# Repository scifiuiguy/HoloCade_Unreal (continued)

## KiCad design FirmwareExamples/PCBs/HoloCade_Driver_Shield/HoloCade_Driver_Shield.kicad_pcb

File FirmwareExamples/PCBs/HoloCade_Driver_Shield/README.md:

# HoloCade Driver Shield

**Also known as:** LBDS, Driver Shield

## Overview

**Motor Control ECU for High-Current Actuator Applications:**

The HoloCade Driver Shield ("LBDS" or "Driver Shield") is a specialized ECU derived from the Universal Shield, designed for high-current motor control applications. It integrates a BTS7960 H-bridge motor driver with hall sensor feedback support, while maintaining the core connectivity features of the Universal Shield (Ethernet, CAN-FD, and aux ports).

<details>
<summary><strong>Driver Shield is a Motor Control ECU</strong></summary>

<div style="margin-left: 20px;">

The Driver Shield is based on the Universal Shield architecture but replaces 4 of the 8 aux ports with an integrated BTS7960 H-bridge motor driver. This enables direct control of high-current linear actuators (such as the PA-HD1-HALL) with integrated hall sensor feedback for position sensing. The shield maintains full compatibility with the Universal Shield's networking and communication features (Ethernet, CAN-FD) while adding dedicated motor control capabilities.

</div>

</details>

<details>
<summary><strong>Key Features</strong></summary>

<div style="margin-left: 20px;">

- Multi-platform support: ESP32-S3 (native) & STM32/Arduino (via personality adapters)
- 4× CAT5 aux ports for child ECUs (Raspberry Pi, Jetson, ESP32, STM32, Arduino)
- Integrated BTS7960 H-bridge motor driver (30A per half-bridge, 60A total)
- Hall sensor feedback support (2× ADC channels for position sensing)
- Isolated CAN-FD transceiver for high-current device control
- 100 Mbps Ethernet connectivity
- 12V/24V input with 5V power distribution (≥5A total capacity)
- 24V motor power rail (direct from input, bypasses buck converter)
- Designed for potting and long-term installations

</div>

</details>

<details>
<summary><strong>High-Level Component Diagram</strong></summary>

<div style="margin-left: 20px;">

```
          ┌────────────────────────────────────────┐
          |                                        │
    ┌─────▲───────┐    ┌───────┐ +5V               │
    │ Barrel Jack │───→│LM2576 │────┐       ┌──────▼───────┐
    │  12V/24V    │    │ Buck  │    │       │ 12/24V Fan   │
    └─────────────┘    └───────┘    │       └───────┬──────┘
         │                │+5V     │               ▼
         │                │        │  ┌────────────────────────┐
         │                │        └─→│         ESP32-S3       │
         │                │           │      (Motherboard)     │
         │                │           └──▲──────────────▲──────┘
         │                │              │              │
         │                │         ┌────▼────┐    ┌────▼────┐
         │                │         │LAN8720A │    │ADM3057E │
         │                │         │Ethernet │    │ CAN-FD  │
         │                │         └────▲────┘    └────▲────┘
         │                │              │              │
         │                │              │         ┌────▼─────┐
         │                │              │         │CAN 3-pin │
         │                │              │         └──────────┘         
         │                │              │
         │                │    ┌─────────▼───────────────┐   
         │                │    │  Aux Ports: J5 J6 J7 J8 │   
         │                │    │  (4× RJ45: Ethernet)    │   
         │                │    └─────────────────────────┘   
         │                │
         │                └──→ 5V to MCU VIN
         │
         └──→ 24V Motor Power Rail
                │
                └──→ Motor Driver Sheet
                      ├─→ BTS7960 H-Bridge (×2)
                      ├─→ 74HC244 Buffer IC
                      ├─→ MBR3045PT Dual-Channel Schottky Diode
                      └─→ Molex 6-pin Actuator Connector (PA-HD1-HALL)
                                              
```

</div>

</details>

<details>
<summary><strong>Project Files</strong></summary>

<div style="margin-left: 20px;">

- **HoloCade_Driver_Shield.kicad_pro** - KiCAD project file
- **HoloCade_Driver_Shield.kicad_sch** - Main schematic file (Sheet 1)
- **motor-driver.kicad_sch** - Motor driver hierarchical sheet (Sheet 2)
- **HoloCade_Driver_Shield.kicad_pcb** - PCB layout file

**Note:** The Driver Shield uses a hierarchical schematic design with the motor driver components on a separate sheet for better organization.

</div>

</details>

<details>
<summary><strong>Power Architecture</strong></summary>

<div style="margin-left: 20px;">

**Hybrid Approach:**
```
12V/24V Input (Barrel Jack)
    ↓
    ├─→ Buck Converter (LM2576: 12V/24V → 5V, 60V max input)
    │       ↓
    │       ├─→ 5V to MCU VIN (via adapter)
    │       │       ↓
    │       │   MCU Onboard Regulator (5V → 3.3V)
    │       │       ↓
    │       │   MCU 3.3V Output (via adapter)
    │       │       └─→ Shield Logic Components (LAN8720A, LEDs)
    │       │
    │       └─→ 5V directly to Aux Port Pins 4 (≥5.0A total across 4 ports)
    │
    └─→ 24V Motor Power Rail (direct passthrough, bypasses buck converter)
            ↓
        Motor Driver Sheet
            ├─→ BTS7960 H-Bridge (×2) - VS pins
            └─→ Actuator Power (MOTOR_A_OUT, MOTOR_B_OUT)
```

**Key Points:**
- Buck converter (LM2576HVS-5) handles 12V/24V input (up to 29.2V for fully charged 24V LiFePO4)
- Aux port power: 5V directly from buck converter (≥5.0A total capacity across 4 ports)
- Motor power: 24V direct passthrough from barrel jack (bypasses buck converter)
- Shield logic: 3.3V from ESP32-S3 pins 1-2 (3.3V_OUT)
- High-current MCUs (ESP32-S3, STM32F407): Adapter routes MCU 3.3V directly
- Low-current MCUs (Arduino): Adapter includes 3.3V regulator (AMS1117-3.3)

</div>

</details>

<details>
<summary><strong>Components</strong></summary>

<div style="margin-left: 20px;">

### Primary Components (Sheet 1 - Shared with Universal Shield)

**Primary ICs (Sheet 1):**
- **U1** - LM2576HVS-5 (TO-220/TO-263) - Buck converter (12V/24V → 5V, ≥5A, 60V max input)
- **U2-U5** - MTJ-883X1 (RJ45 aux ports J5-J8, references U2, U3, U4, U5 in schematic)
- **U6** - ESP32-S3-2x22 (MCU interface, 44-pin header)
- **U7** - ADM3057ExRW - Isolated CAN-FD transceiver (3kV isolation)
- **U8** - LAN8720A (QFN-32) - 100 Mbps Ethernet PHY
  - Management: MDC/MDIO to MCU via adapter
  - Clock: External 25MHz crystal (3225 SMD recommended, Y1)
  - Reset: ESP32-S3 EN pin (GPIO3) or separate GPIO

**3.3V Power:** ESP32-S3 pins 1-2 (3.3V_OUT) provide 3.3V for shield logic components. No separate 3.3V LDO required for ESP32-S3.
- VIO: +3.3V (logic supply) - decoupled with C14 (100nF)
- VCC: +5V (isoPower supply) - decoupled with C15 (100nF) and C16 (4.7µF tantalum)
- VISOOUT → VISOIN (Kelvin jumper required on PCB layout)
- VISOIN/VISOOUT: Isolated supply - decoupled with C17 (100nF) and C18 (4.7µF tantalum)
- CAN termination: 120Ω resistor (R12) switchable via SW1 (DIP switch) across CANH/CANL

**LEDs (3 total):**
- Power LED (Red): +3.3V → R4 (270Ω) → D1 → GND
- Ethernet Link LED (Green): LAN8720A LED1 → R5 (270Ω) → D2 → GND
- Ethernet Speed LED (Green): LAN8720A LED2 → R6 (270Ω) → D3 → GND

**Resistors (Sheet 1 - standard components):**

| Reference | Value | Purpose | Notes |
|-----------|-------|---------|-------|
| R1 | 10 kΩ | Polarity protection MOSFET gate pull-down | Pulls gate of IRF9540N P-channel MOSFET to GND for reverse polarity protection |
| R2 | 1 kΩ | Buck converter voltage divider (upper) | Forms feedback divider with R3 for LM2576 output regulation |
| R3 | 326Ω | Buck converter voltage divider (lower) | Forms feedback divider with R2 for LM2576 5V output regulation |
| R4 | 270Ω | Power LED current limiting | Limits current through red power indicator LED (D1) |
| R5 | 270Ω | Ethernet Link LED current limiting | Limits current through green LAN LED1 (D2, link status) |
| R6 | 270Ω | Ethernet Speed LED current limiting | Limits current through green LAN LED2 (D3, speed indicator) |
| R7 | 49.9Ω (49R9) | LAN8720A RBIAS pull-down | Sets bias current for LAN8720A internal reference |
| R8 | 10 kΩ | ESP32-S3 RESET_N pull-up | Pull-up resistor for LAN8720A RESET_N pin (active LOW) |
| R9 | 4.7 kΩ | LAN8720A MDIO pull-up | Pull-up resistor for ESP32-S3 GPIO18 (MDIO) management interface |
| R10 | 100Ω | Fan FET gate resistor | Current limiting resistor for IRLZ44N MOSFET gate drive (GPIO42) |
| R11 | 10 kΩ | Fan FET gate pull-down | Pull-down resistor for fan MOSFET gate (prevents floating when GPIO42 is high-Z) |
| R12 | 120Ω | CAN bus termination resistor | Switchable termination resistor across CANH/CANL (via SW1) |

**Capacitors (Sheet 1 - standard components):**

| Reference | Value | Type | Purpose | Notes |
|-----------|-------|------|---------|-------|
| C1 | 100nF | Non-polarized | Barrel jack output decoupling | High-frequency noise filtering on power input |
| C2 | 10µF | Polarized | Barrel jack output decoupling | Bulk capacitance for power input smoothing |
| C3 | 100nF | Non-polarized | Buck converter input decoupling | High-frequency noise filtering on LM2576 input |
| C4 | 100nF | Non-polarized | Buck converter output decoupling | High-frequency noise filtering on 5V output |
| C5 | 10µF | Polarized | Buck converter output decoupling | Bulk capacitance for 5V output smoothing |
| C6 | 10µF | Polarized | ESP32-S3 3.3V output decoupling | Bulk capacitance for ESP32 3.3V_OUT smoothing |
| C7 | 100nF | Non-polarized | ESP32-S3 3.3V output decoupling | High-frequency noise filtering on ESP32 3.3V_OUT |
| C8 | 100nF | Non-polarized | LAN8720A VDD2 decoupling | Power supply decoupling for LAN8720A VDD2 pin |
| C9 | 100nF | Non-polarized | LAN8720A VDDCR decoupling | Power supply decoupling for LAN8720A VDDCR pin |
| C10 | 100nF | Non-polarized | LAN8720A VDD1A decoupling | Power supply decoupling for LAN8720A VDD1A pin |
| C11 | 100nF | Non-polarized | LAN8720A VDDIO decoupling | Power supply decoupling for LAN8720A VDDIO pin |
| C12 | 10pF | Non-polarized | 25MHz crystal load capacitor (XTAL1) | Crystal oscillator load capacitor for XTAL1 |
| C13 | 10pF | Non-polarized | 25MHz crystal load capacitor (XTAL2) | Crystal oscillator load capacitor for XTAL2 |
| C14 | 100nF | Non-polarized | ADM3057E VIO decoupling | High-frequency noise filtering on CAN transceiver logic supply |
| C15 | 100nF | Non-polarized | ADM3057E VCC decoupling | High-frequency noise filtering on CAN transceiver isoPower supply |
| C16 | 4.7µF | Polarized (Tantalum) | ADM3057E VCC bulk decoupling | Bulk capacitance for CAN transceiver isoPower supply smoothing |
| C17 | 100nF | Non-polarized | ADM3057E VISO decoupling | High-frequency noise filtering on CAN transceiver isolated supply (VISOIN/VISOOUT) |
| C18 | 4.7µF | Polarized (Tantalum) | ADM3057E VISO bulk decoupling | Bulk capacitance for CAN transceiver isolated supply smoothing |

**Diodes (Sheet 1 - standard components):**

| Reference | Type | Value | Purpose | Notes |
|-----------|------|-------|---------|-------|
| D1 | LED | LED | Red status LED for 3V power | Power indicator LED, current limited by R4 (270Ω) |
| D2 | LED | LED | Green status LED for LAN LED1 pin | Ethernet link status indicator, driven by LAN8720A LED1, current limited by R5 (270Ω) |
| D3 | LED | LED | Green status LED for LAN LED2 pin | Ethernet speed indicator, driven by LAN8720A LED2, current limited by R6 (270Ω) |
| D4 | Schottky Diode | SS14 | Flyback diode for MCU fan protection | Protects MCU from inductive kickback when fan MOSFET switches off (cathode on +VIN, anode on FAN_SW) |
| D5 | Zener Diode | BZX84C12 | Polarity protection MOSFET gate protection | 12V zener diode protects IRF9540N gate from overvoltage (cathode to gate, anode to source) |
| D6-D8 | Schottky Diode | MBR735 | Aux port power protection | Reverse polarity protection for aux port power pins (J5-J7) |
| D9 | Schottky Diode | SS14 | Aux port power protection | Reverse polarity protection for aux port power pin (J8) |

**MOSFETs (Sheet 1 - standard components):**

| Reference | Type | Part Number | Purpose | Notes |
|-----------|------|-------------|---------|-------|
| Q1 | P-channel MOSFET | IRF9540N | Reverse polarity protection | High-side switch at barrel jack input. Source to +24_12V, Drain to buck converter input. Gate pulled to GND via R1 (10kΩ) with zener protection (D5). Prevents damage from inverted power supply connections. |
| Q2 | N-channel MOSFET | IRLZ44N | Fan control switch | Low-side switch for 12/24V fan. Drain to FAN_SW, Source to GND. Gate driven by ESP32-S3 GPIO42 via R10 (100Ω). Gate pull-down via R11 (10kΩ). Flyback diode D4 protects from inductive kickback. |

**Switches (Sheet 1 - standard components):**

| Reference | Type | Part Number | Purpose | Notes |
|-----------|------|-------------|---------|-------|
| SW1 | DIP Switch | SW_DIP_x01 | CAN bus termination control | Single-pole switch to enable/disable 120Ω termination resistor (R12) across CANH/CANL. Required for proper CAN bus operation (only end nodes should have termination). |
| SW2-SW5 | DIP Switch | SW_DIP_x01 | Aux port power switches | Power enable switches for aux ports J5-J8 (J5_PWR_SW, J6_PWR_SW, J7_PWR_SW, J8_PWR_SW) |

### Motor Driver Components (Sheet 2 - Hierarchical Motor Driver Sheet)

**Motor Driver ICs:**
- **BTS7960B** (×2) - Half-bridge motor driver (30A per IC, 60A total in H-bridge configuration)
  - Package: TO-263-7 (DPAK127P1490X440-8N)
  - VS: 24V motor power rail (pins 1, 7, 8 - thermal tab)
  - OUT: Motor output (pin 4/5)
  - IN: PWM control input (pin 2)
  - INH: Enable input (pin 3)
  - IS: Current sense output (pin 6)
  - SR: Slew rate control (pin 5, unused, tied to GND via pull-down)

**Buffer IC:**
- **74HC244** - Octal buffer/line driver (TSSOP-20 package)
  - Purpose: Signal isolation and drive strength between ESP32-S3 and BTS7960
  - Supply: 3.3V (from ESP32-S3 3.3V_OUT)
  - Inputs: ESP32-S3 GPIO pins (MOTOR_A_EN, MOTOR_A_IN, MOTOR_B_EN, MOTOR_B_IN)
  - Outputs: BTS7960 IN and INH pins

**Schottky Diodes:**
- **D10** - MBR3045PT - Dual common-cathode Schottky diode (30A per diode, 15A per anode)
  - Package: TO-220-3
  - Purpose: Flyback protection for motor driver (dissipates inductive kickback)
  - Configuration: Common cathode to motor power rail, anodes to MOTOR_A_OUT and MOTOR_B_OUT
  - Note: Only one MBR3045PT is used (not two separate diodes) as it contains two diodes in a single package

**Motor Driver Resistors:**

| Reference | Value | Purpose | Notes |
|-----------|-------|---------|-------|
| R13-R16 | 10 kΩ | BTS7960 INH pull-down | Pull-down resistors for enable pins (INH) on both BTS7960 ICs |
| R17-R18 | 2.2 kΩ | Current sense voltage divider (upper) | Forms voltage divider with R19-R20 to scale 0-5V current sense to 0-3.3V for ESP32 ADC |
| R19-R20 | 220Ω | Current sense voltage divider (lower) | Forms voltage divider with R17-R18 for ESP32 ADC compatibility |
| R21-R22 | 10 kΩ | Hall sensor pull-up | Pull-up resistors for hall sensor data lines (HALL1, HALL2) |

**Motor Driver Capacitors:**

| Reference | Value | Type | Purpose | Notes |
|-----------|-------|------|---------|-------|
| C19 | 100nF | Non-polarized | BTS7960 decoupling (U9) | High-frequency noise filtering on VS pin of first BTS7960 IC |
| C20 | 47µF | Polarized | Motor power bulk capacitance (U9) | Bulk capacitance for 24V motor power rail smoothing near first BTS7960 IC |
| C21 | 100nF | Non-polarized | BTS7960 decoupling (U10) | High-frequency noise filtering on VS pin of second BTS7960 IC |
| C22 | 47µF | Polarized | Motor power bulk capacitance (U10) | Bulk capacitance for 24V motor power rail smoothing near second BTS7960 IC |

### Connectors (Sheet 1)

**Power:**
- **Schematic Symbol:** Kycon KLDX-0202-A (horizontal mount, 2.0mm center pin) - Used in schematic because footprint is available in KiCad built-in libraries. Pin pattern is identical to vertical mount variant.
- **BOM Part (Manufacturing):** Kycon KLDVX-0202-A (vertical mount, 2.0mm center pin, ~15-20mm shell height) - **Use this for actual PCB assembly.** Vertical mount is required for potting compatibility. Barrel orientation is 90° from mount plane (vertical) vs. parallel (horizontal) for KLDX variant.
- **Note:** The KLDX-0202-A symbol can be used in schematic, but order KLDVX-0202-A for manufacturing. The barrel jack can be ordered separately and excluded from BOM during manufacture if necessary.
- 12V/24V header: Passthrough for motors/solenoids
- 5V header: To MCU VIN (via adapter)

### Optional MCU Cooling Fan

- **Mechanical**:
  - Add a large through-hole window directly under the MCU socket so airflow can pass through the board when a fan is mounted below the module.
  - Flank the 44-pin MCU header with four plated mounting holes (M2/M2.5) laid out on a 40×40 mm square to accept standard standoffs for 40 mm fans. The same pattern works for top- or bottom-mounted fans; leave clearance for the ESP32 heat shield.
- **Electrical**:
  - Add a **JST-XH 2-pin** header near the MCU slot labelled `FAN_PWR` (Pin 1 = +VIN 12/24 V, Pin 2 = FAN_SW).
  - Route Pin 1 to the raw 12 V/24 V rail immediately after the barrel jack (ahead of the LM2576 buck) with the same fuse/polyswitch protection as the rest of the VIN net.
  - Route Pin 2 to the drain of **IRLZ44N** N-channel MOSFET (Q2) so the MCU can switch the low side of the fan; tie the source to GND and add a 10 kΩ gate pull-down (R11) plus 100 Ω gate resistor (R10).
  - Place a flyback diode (SS14, D4) across the fan connector (cathode on +VIN, anode on FAN_SW) to clamp inductive kick when the MOSFET turns off.
  - Provide a 0.1 µF/50 V snubber capacitor near the connector if the harness run is long (>0.5 m).
  - Connect ESP32-S3 `GPIO42` (Pad 26) to the MOSFET gate via the adapter header. This GPIO is reserved for `FAN_CTRL` and supports high-current drive. Other MCUs can remap as needed.
  - Label the net `FAN_CTRL` so firmware can PWM the fan if desired; recommend a 25 kHz PWM to stay out of the audible band.

**Ethernet:**
- **Adam Tech MTJ-883X1** (4× aux ports) - RJ45 jack, vertical mount, 16.38mm shell height
- **Aux Ports:** J5, J6, J7, J8 (schematic references U2, U3, U4, U5)
- **Note:** Pins 7 and 8 on all aux ports have been remapped compared to Universal Shield:
  - Pin 7 (ADC): Now uses GPIO1 (J6) and GPIO7 (J7) instead of GPIO4 and GPIO5
  - Pin 8 (PWM): Now uses GPIO4 (J5) and GPIO5 (J6) instead of GPIO1 and GPIO2
  - This remapping improves routing on the Driver Shield PCB and frees GPIO4/5 for motor driver current sense

**CAN Bus:**
- **JST-XH 3-pin connector** (vibration-resistant alternatives: Phoenix Contact MSTB, Deutsch DT, Molex MX150, or JST EH)
- Pin 1: CANH
- Pin 2: CANL
- Pin 3: CAN_GND (always routed on PCB, even if unused in 2-wire networks)

**MCU Interface:**
- **44-pin 2×22 stacking female header** - ESP32-S3 socket/through-hole footprint

**Motor Actuator Connector (Sheet 2 - Motor Driver Sheet):**
- **J5** - Molex 1724480006 - 6-pin connector for PA-HD1-HALL linear actuator
- Pin 1: +24V (motor power positive)
- Pin 2: 24V GND (motor power ground)
- Pin 3: +5V (hall sensor power)
- Pin 4: 5V GND (hall sensor ground)
- Pin 5: HALL1 (hall sensor data 1, to ESP32-S3 GPIO9 via voltage divider)
- Pin 6: HALL2 (hall sensor data 2, to ESP32-S3 GPIO10 via voltage divider)

**UART Debug Breakout (4-pin header):** ✅ **AVAILABLE**
- **Status:** Implemented and available on Driver Shield
- **Purpose:** Serial debug interface for low-level debugging, firmware programming, and module interfacing
- **Pinout:**
  - Pin 1: GND (Ground)
  - Pin 2: +3.3V (Power supply for debug modules)
  - Pin 3: U0TXD (GPIO43, UART0 TX - serial transmit)
  - Pin 4: U0RXD (GPIO44, UART0 RX - serial receive)

### Enclosure

**Standard Project Box:**
- **Polycase LP-70F** - ABS plastic enclosure designed for the Driver Shield
- **External dimensions:** 5.5 × 4.2 × 1.7 inches (139.7 × 106.7 × 43.2 mm)
- **Internal dimensions:** 5.25 × 4.0 × 1.6 inches (133.4 × 101.6 × 40.6 mm)
- **Features:**
  - Molded-on flanges for surface mounting
  - PCB mounting bosses in the base
  - PCB template available from Polycase for design reference
- **Product page:** [Polycase LP-70F](https://www.polycase.com/lp-70F)
- **Mounting holes:** PCB corner mounting holes are sized for standard case mounting bosses (typically M2/M2.5/M3 threaded inserts)
- **Mounting hole spacing:** 4.13" × 2.88" (mounting boss centers)
- **PCB mounting:** PCB feet/standoffs elevate the board 0.125" (1/8") above the case floor

**Potting Design:**
- **Connector orientation:** All pluggable elements (RJ45 connectors, barrel jack, headers, Molex connector) are oriented vertically (perpendicular to PCB plane) to facilitate potting and prevent compound from entering connector cavities during encapsulation.
- **Potting process:** Potting involves filling the enclosure with a protective compound that encapsulates the PCB and components, providing environmental protection (moisture, dust, vibration), electrical insulation, and thermal management. The compound cures to form a solid, protective barrier around the electronics. For the Driver Shield, potting is recommended for long-term installations in harsh environments (outdoor, industrial, automotive applications).
- **Recommended potting compound:** Two-part polyurethane potting compound (e.g., MG Chemicals 832TC, Smooth-On Smooth-Cast 300, or similar) is recommended. Polyurethane offers good thermal conductivity, flexibility to accommodate thermal expansion, and resistance to moisture and chemicals. Avoid rigid epoxies for this application as they can crack under thermal cycling. Select a compound with a working time (pot life) of 15-30 minutes to allow proper mixing and pouring, and ensure it's rated for the operating temperature range of your installation.
- **Potting compound volume:** To submerge the top of the PCB by at least 1/16" (0.0625"), approximately **4.5-5.0 cubic inches** of potting compound is required. This accounts for the case interior (5.25" × 4.0"), PCB standoff height (0.125"), PCB thickness (~0.062"), and minimum coverage depth (0.0625"), minus the volume displaced by the PCB and components. Order slightly more than calculated (10-20% extra) to account for mixing waste and ensure complete coverage.
- **Connector:** Standard 2.54mm pitch (0.1") header, recommended 4-pin male header for breadboard/prototyping
- **Common Uses:**
  - Serial debug console (USB-to-serial adapters: FTDI, CP2102, CH340, etc.)
  - Serial terminal interfaces (PuTTY, minicom, screen, etc.)
  - Logic analyzers for signal debugging
  - Firmware programming/bootloaders
  - Interfacing with UART-based modules:
    - Bluetooth modules (HC-05, HC-06, ESP32-BLE, etc.)
    - WiFi modules (ESP8266, some ESP32 variants)
    - GPS modules (NEO-6M, NEO-8M, etc.)
    - LoRa modules (SX1278, SX1262)
    - RFID readers (MFRC522, PN532)
    - Barcode scanners
    - Serial LCD displays
    - Motor controllers
    - Industrial sensors
    - Many other embedded modules requiring point-to-point serial communication
- **Note:** UART is one of the most versatile communication protocols for embedded systems, supporting a wide variety of components and debug tools. While the 4 Ethernet ports provide network-level debugging, the UART breakout provides low-level serial debugging and direct module interfacing.

</div>

</details>

<details>
<summary><strong>Pin Mappings</strong></summary>

<div style="margin-left: 20px;">

### ESP32-S3-WROOM-1 Complete 44-Pin Pinout (2×22 Header)

**Pin Numbering:** Left column (pins 1-22) top to bottom, right column (pins 23-44) top to bottom.

| Pin | GPIO | Function | Notes |
|-----|------|----------|-------|
| 1 | - | 3.3V_OUT | 3.3V power output (from onboard regulator) |
| 2 | - | 3.3V_OUT | 3.3V power output (from onboard regulator) |
| 3 | GPIO3 | EN | Enable (active HIGH, reset when LOW) |
| 4 | GPIO4 | GPIO4 / ADC1_CH3 | Motor A Current Sense (MOTOR_A_IS) |
| 5 | GPIO5 | GPIO5 / ADC1_CH4 | Motor B Current Sense (MOTOR_B_IS) |
| 6 | GPIO6 | GPIO6 / ADC1_CH5 | Aux Port 8 ADC |
| 7 | GPIO7 | GPIO7 / ADC1_CH6 | Aux Port 7 ADC |
| 8 | GPIO15 | GPIO15 / LEDC_CH3 | Aux Port 8 PWM |
| 9 | GPIO16 | GPIO16 / LEDC_CH4 | Aux Port 5 PWM |
| 10 | GPIO17 | GPIO17 | LAN8720A MDC (Ethernet management clock) |
| 11 | GPIO18 | GPIO18 | LAN8720A MDIO (Ethernet management data) |
| 12 | GPIO8 | GPIO8 / ADC1_CH7 | Aux Port 5 ADC |
| 13 | GPIO3 | GPIO3 | General purpose I/O (also EN function on pin 3) |
| 14 | GPIO46 | GPIO46 | General purpose I/O (E-Stop interrupt capable) |
| 15 | GPIO9 | GPIO9 / ADC1_CH8 | Hall Sensor 1 (HALL1) |
| 16 | GPIO10 | GPIO10 / ADC1_CH9 | Hall Sensor 2 (HALL2) |
| 17 | GPIO11 | GPIO11 / LEDC_CH4 | Motor A PWM (MOTOR_A_IN) |
| 18 | GPIO12 | GPIO12 / LEDC_CH0 | Motor A Enable (MOTOR_A_EN) |
| 19 | GPIO13 | GPIO13 / LEDC_CH1 | Motor B PWM (MOTOR_B_IN) |
| 20 | GPIO14 | GPIO14 / LEDC_CH2 | Motor B Enable (MOTOR_B_EN) |
| 21 | - | VIN | 5V power input (to onboard regulator) |
| 22 | - | GND | Ground |
| 23 | - | GND | Ground |
| 24 | GPIO43 | U0TXD | UART0 TX (GPIO43) |
| 25 | - | NC | No Connect |
| 26 | GPIO1 | GPIO1 / ADC1_CH0 | Aux Port 6 ADC (remapped from GPIO4) |
| 27 | GPIO2 | GPIO2 / LEDC_CH6 | Aux Port 7 PWM (remapped from GPIO5) |
| 28 | GPIO42 | GPIO42 / Pad 26 | General purpose I/O (reserved for FAN_CTRL per README) |
| 29 | GPIO41 | GPIO41 / Pad 29 | CAN RXD (ADM3057E) |
| 30 | GPIO40 | GPIO40 / Pad 30 | CAN TXD (ADM3057E) |
| 31 | GPIO39 | GPIO39 | LAN8720A TXD0 (Ethernet transmit data 0) |
| 32 | GPIO38 | GPIO38 | General purpose I/O |
| 33 | GPIO37 | GPIO37 | General purpose I/O |
| 34 | GPIO36 | GPIO36 | General purpose I/O |
| 35 | GPIO35 | GPIO35 | General purpose I/O |
| 36 | GPIO0 | GPIO0 / ADC1_CH0 | Boot strap pin (unused, kept free to avoid boot mode conflicts) |
| 37 | GPIO45 | GPIO45 | General purpose I/O (E-Stop interrupt capable) |
| 38 | GPIO46 | GPIO46 | General purpose I/O (E-Stop interrupt capable) |
| 39 | GPIO47 | GPIO47 | General purpose I/O (E-Stop interrupt capable) |
| 40 | GPIO21 | GPIO21 / LEDC_CH7 | Aux Port 6 PWM |
| 41 | GPIO20 | GPIO20 | General purpose I/O |
| 42 | GPIO44 | U0RXD | UART0 RX (GPIO44) |
| 43 | - | GND | Ground |
| 44 | - | GND | Ground |

**Note:** This pinout is based on standard ESP32-S3-WROOM-1 dev board layouts. Verify against your specific board's datasheet. GPIO assignments for Aux Ports, Motor Driver, Ethernet, and CAN match the mappings documented below.

### ESP32-S3 Electrical Type Map (KiCad Pin Properties)

**Use this map to set the "Electrical type" property for each pin in your ESP32-S3 symbol:**

| Pin | GPIO | Electrical Type | Reason |
|-----|------|----------------|--------|
| 1 | - | Power output | 3.3V_OUT (power source) |
| 2 | - | Power output | 3.3V_OUT (power source) |
| 3 | GPIO3 | Input | EN (enable/reset input) |
| 4 | GPIO4 | Input | ADC pin (analog input) - Motor A Current Sense |
| 5 | GPIO5 | Input | ADC pin (analog input) - Motor B Current Sense |
| 6 | GPIO6 | Input | ADC pin (analog input) - Aux Port 8 ADC |
| 7 | GPIO7 | Input | ADC pin (analog input) - Aux Port 7 ADC |
| 8 | GPIO15 | Output | PWM output (LEDC_CH3) - Aux Port 8 PWM |
| 9 | GPIO16 | Output | PWM output (LEDC_CH4) - Aux Port 5 PWM |
| 10 | GPIO17 | Bidirectional | MDC (I2C-like, bidirectional) |
| 11 | GPIO18 | Bidirectional | MDIO (I2C-like, bidirectional) |
| 12 | GPIO8 | Input | ADC pin (analog input) - Aux Port 5 ADC |
| 13 | GPIO3 | Bidirectional | General purpose I/O (also EN function) |
| 14 | GPIO46 | Bidirectional | General purpose I/O (E-Stop interrupt capable) |
| 15 | GPIO9 | Input | ADC pin (analog input) - Hall Sensor 1 |
| 16 | GPIO10 | Input | ADC pin (analog input) - Hall Sensor 2 |
| 17 | GPIO11 | Output | PWM output (LEDC_CH4) - Motor A PWM |
| 18 | GPIO12 | Output | Digital output - Motor A Enable |
| 19 | GPIO13 | Output | PWM output (LEDC_CH1) - Motor B PWM |
| 20 | GPIO14 | Output | Digital output - Motor B Enable |
| 21 | - | Power input | VIN (5V power input) |
| 22 | - | Power input | GND (ground) |
| 23 | - | Power input | GND (ground) |
| 24 | GPIO43 | Output | UART0 TX (serial transmit) |
| 25 | - | Unspecified | NC (No Connect) |
| 26 | GPIO1 | Input | ADC pin (analog input) - Aux Port 6 ADC |
| 27 | GPIO2 | Output | PWM output (LEDC_CH6) - Aux Port 7 PWM |
| 28 | GPIO42 | Bidirectional | General purpose I/O (reserved for FAN_CTRL) |
| 29 | GPIO41 | Bidirectional | CAN RXD (bidirectional CAN receive) |
| 30 | GPIO40 | Bidirectional | CAN TXD (bidirectional CAN transmit) |
| 31 | GPIO39 | Output | LAN8720A TXD0 (Ethernet transmit data 0) |
| 32 | GPIO38 | Bidirectional | General purpose I/O |
| 33 | GPIO37 | Bidirectional | General purpose I/O |
| 34 | GPIO36 | Bidirectional | General purpose I/O |
| 35 | GPIO35 | Bidirectional | General purpose I/O |
| 36 | GPIO0 | Input | General purpose I/O (boot strap pin, unused) |
| 37 | GPIO45 | Bidirectional | General purpose I/O (E-Stop interrupt capable) |
| 38 | GPIO46 | Bidirectional | General purpose I/O (E-Stop interrupt capable) |
| 39 | GPIO47 | Bidirectional | General purpose I/O (E-Stop interrupt capable) |
| 40 | GPIO21 | Output | PWM output (LEDC_CH7) - Aux Port 6 PWM |
| 41 | GPIO20 | Bidirectional | General purpose I/O |
| 42 | GPIO44 | Input | UART0 RX (serial receive) |
| 43 | - | Power input | GND (ground) |
| 44 | - | Power input | GND (ground) |

**Summary:**
- **Power output**: Pins 1, 2 (3.3V_OUT)
- **Power input**: Pin 21 (VIN), Pins 22, 23, 43, 44 (GND)
- **Input**: Pins 3 (EN), 4-7, 12, 15-16, 26 (ADC pins), 42 (UART0 RX)
- **Output**: Pins 8-9, 17-20, 24 (UART0 TX), 27, 31, 40 (PWM/digital outputs)
- **Bidirectional**: Pins 10-11 (MDC/MDIO), 13-14, 28-30 (CAN), 32-35, 37-39 (general GPIOs)
- **Unspecified**: Pin 25 (NC)
- **Unused**: Pin 36 (GPIO0 - boot strap pin, kept free to avoid boot mode conflicts)

### ESP32-S3 Aux Port ADC/PWM (J5-J8 only)

| Aux Port | ADC GPIO | ADC Pin | ADC Channel | PWM GPIO | PWM Pin | PWM LEDC Channel |
|----------|----------|---------|-------------|----------|---------|------------------|
| J5 | GPIO8 | Pin 12 | ADC1_CH7 | GPIO16 | Pin 9 | LEDC_CH4 |
| J6 | GPIO1 | Pin 26 | ADC1_CH0 | GPIO21 | Pin 40 | LEDC_CH7 |
| J7 | GPIO7 | Pin 7 | ADC1_CH6 | GPIO2 | Pin 27 | LEDC_CH6 |
| J8 | GPIO6 | Pin 6 | ADC1_CH5 | GPIO15 | Pin 8 | LEDC_CH3 |

**Note:** Pins 7 and 8 on all aux ports have been remapped compared to Universal Shield:
- **Pin 7 (ADC):** Now uses GPIO1 (J6) and GPIO7 (J7) instead of GPIO4 and GPIO5
- **Pin 8 (PWM):** Now uses GPIO4 (J5) and GPIO5 (J6) instead of GPIO1 and GPIO2
- This remapping improves PCB routing and frees GPIO4/5 for motor driver current sense

**KiCAD Net Labels:**
- ADC: `AUX5_ADC`, `AUX6_ADC`, `AUX7_ADC`, `AUX8_ADC`
- PWM: `AUX5_PWM`, `AUX6_PWM`, `AUX7_PWM`, `AUX8_PWM`

### Motor Driver Pin Mappings

**BTS7960 H-Bridge Control:**

| Signal | ESP32-S3 GPIO | ESP32-S3 Pin | Function | Notes |
|--------|---------------|--------------|----------|-------|
| MOTOR_A_EN | GPIO12 | Pin 18 | Motor A Enable | Digital output, via 74HC244 buffer |
| MOTOR_A_IN | GPIO11 | Pin 17 | Motor A PWM | PWM output (LEDC_CH4), via 74HC244 buffer |
| MOTOR_A_IS | GPIO4 | Pin 4 | Motor A Current Sense | ADC input (ADC1_CH3), via voltage divider (2.2kΩ/220Ω) |
| MOTOR_B_EN | GPIO14 | Pin 20 | Motor B Enable | Digital output, via 74HC244 buffer |
| MOTOR_B_IN | GPIO13 | Pin 19 | Motor B PWM | PWM output (LEDC_CH1), via 74HC244 buffer |
| MOTOR_B_IS | GPIO5 | Pin 5 | Motor B Current Sense | ADC input (ADC1_CH4), via voltage divider (2.2kΩ/220Ω) |

**Hall Sensor Feedback:**

| Signal | ESP32-S3 GPIO | ESP32-S3 Pin | Function | Notes |
|--------|---------------|--------------|----------|-------|
| HALL1 | GPIO9 | Pin 15 | Hall Sensor 1 | ADC input (ADC1_CH8), via voltage divider (10kΩ pull-up, 2.2kΩ/220Ω divider) |
| HALL2 | GPIO10 | Pin 16 | Hall Sensor 2 | ADC input (ADC1_CH9), via voltage divider (10kΩ pull-up, 2.2kΩ/220Ω divider) |

**Molex 6-Pin Actuator Connector (J5):**

| Pin | Signal | Connection | Function | Notes |
|-----|--------|------------|----------|-------|
| 1 | MOTOR_PWR | +24V rail | Motor power positive | 24V motor power supply (direct from barrel jack, bypasses buck converter) |
| 2 | MOTOR_GND | GND | Motor power ground | Motor power return path |
| 3 | HALL_PWR | +5V | Hall sensor power | 5V supply for hall sensor electronics (from buck converter 5V output) |
| 4 | HALL_GND | GND | Hall sensor ground | Hall sensor power return path |
| 5 | HALL1 | ESP32-S3 GPIO9 | Hall Sensor 1 data | ADC input (ADC1_CH8), via voltage divider (10kΩ pull-up, 2.2kΩ/220Ω divider) |
| 6 | HALL2 | ESP32-S3 GPIO10 | Hall Sensor 2 data | ADC input (ADC1_CH9), via voltage divider (10kΩ pull-up, 2.2kΩ/220Ω divider) |

**Note:** Pin mapping is based on the PA-HD1-HALL linear actuator datasheet. The connector (Molex 1724480006) is a 6-pin connector that matches the actuator's wiring harness. Motor power (pins 1-2) is controlled via the BTS7960 H-bridge outputs (MOTOR_A_OUT, MOTOR_B_OUT), while hall sensor feedback (pins 5-6) provides position feedback to the ESP32-S3 ADC inputs.

**74HC244 Buffer IC Pin Mapping:**

| 74HC244 Pin | Signal | Connection | Notes |
|-------------|--------|------------|-------|
| 1A0 | MOTOR_A_EN | ESP32-S3 GPIO12 | Enable signal for Motor A |
| 1Y0 | BTS_A_EN | BTS7960 INH (Motor A) | Buffered enable output |
| 1A1 | MOTOR_A_IN | ESP32-S3 GPIO11 | PWM signal for Motor A |
| 1Y1 | BTS_A_IN | BTS7960 IN (Motor A) | Buffered PWM output |
| 1A2 | MOTOR_B_EN | ESP32-S3 GPIO14 | Enable signal for Motor B |
| 1Y2 | BTS_B_EN | BTS7960 INH (Motor B) | Buffered enable output |
| 1A3 | MOTOR_B_IN | ESP32-S3 GPIO13 | PWM signal for Motor B |
| 1Y3 | BTS_B_IN | BTS7960 IN (Motor B) | Buffered PWM output |
| VCC | +3.3V | ESP32-S3 3.3V_OUT | Buffer IC power supply |
| GND | GND | Common ground | Buffer IC ground |

**Note:** The 74HC244 provides signal isolation and increased drive strength between the ESP32-S3 and BTS7960 ICs, ensuring reliable control signal transmission.

### LAN8720A Ethernet PHY

**MII/RMII Interface (Ethernet Data):**

| LAN8720A Pin | ESP32-S3 GPIO | ESP32-S3 Pin | Function | Notes |
|--------------|---------------|--------------|----------|-------|
| TXD0 | GPIO39 | Pin 31 | Transmit Data 0 | RMII transmit data bit 0 |
| TXD1 | GPIO37 | Pin 33 | Transmit Data 1 | RMII transmit data bit 1 |
| TXEN | GPIO20 | Pin 41 | Transmit Enable | RMII transmit enable |
| RXD0 | GPIO35 | Pin 35 | Receive Data 0 | RMII receive data bit 0 |
| RXD1 | GPIO36 | Pin 34 | Receive Data 1 | RMII receive data bit 1 |
| RXER | - | - | Receive Error | No Connect (NC) |
| CRS_DV | GPIO38 | Pin 32 | Carrier Sense / Data Valid | RMII carrier sense and data valid |
| REF_CLK | - | - | Reference Clock | No Connect (NC) - LAN8720A uses external 25MHz crystal |

**Management Interface (SMI):**

| LAN8720A Pin | ESP32-S3 GPIO | ESP32-S3 Pin | Function | Notes |
|--------------|---------------|--------------|----------|-------|
| MDC | GPIO17 | Pin 10 | Management Data Clock | SMI clock signal |
| MDIO | GPIO18 | Pin 11 | Management Data I/O | SMI bidirectional data |

**Control Signals:**

| LAN8720A Pin | ESP32-S3 GPIO | ESP32-S3 Pin | Function | Notes |
|--------------|---------------|--------------|----------|-------|
| RESET_N | EN (GPIO3) | Pin 3 | Reset (active LOW) | Reset control, active LOW |
| INT | - | - | Interrupt | No Connect (NC) |

**Clock:**

| LAN8720A Pin | Connection | Notes |
|--------------|------------|-------|
| XTAL1 | External 25MHz crystal (3225 SMD recommended) | Crystal connection |
| XTAL2 | External 25MHz crystal (3225 SMD recommended) | Crystal connection |
| - | 10pF decoupling capacitors | One capacitor from XTAL1 to GND, one from XTAL2 to GND |
| Exposed pad (VSS) | Ground pour + thermal vias | Stitch the VQFN thermal pad to the 3.3 V ground plane during PCB layout for heat spreading and signal reference |

**Ethernet Differential Signals (to RJ45 Connectors):**

| LAN8720A Pin | Destination | Notes |
|--------------|-------------|-------|
| TXP/TXN | All 4 aux ports pins 1-2 | Transmit differential pair |
| RXP/RXN | All 4 aux ports pins 3, 6 | Receive differential pair |

### ADM3057E CAN Transceiver

| ADM3057E Pin | ESP32-S3 Connection | Notes |
|--------------|---------------------|-------|
| TXD | GPIO40 (Pad 30) | CAN transmit |
| RXD | GPIO41 (Pad 29) | CAN receive |
| STBY | +3.3V (tie high) | Normal operation |
| SILENT | GND (tie low) | Normal operation |
| RS | GND (tie low) | Normal mode |
| VIO | +3.3V | Logic supply |
| VCC | +5V | isoPower supply |
| VISOOUT | Jump to VISOIN | Required |
| VISOIN | Jump to VISOOUT | Required |
| CANH | CAN connector Pin 1 | Bus high |
| CANL | CAN connector Pin 2 | Bus low |
| GNDISO | CAN connector Pin 3 | Isolated ground |

**Note:** GPIO4/5 are used for motor driver current sense, so CAN uses GPIO40/41 (same as Universal Shield).

</div>

</details>

<details>
<summary><strong>Aux Port Pinout (CAT5 T568B)</strong></summary>

<div style="margin-left: 20px;">

| RJ45 Pin | T568B Color | Signal | Connection |
|----------|-------------|--------|------------|
| 1 | Orange/White | Ethernet TX+ | LAN8720A TXP |
| 2 | Orange | Ethernet TX- | LAN8720A TXN |
| 3 | Green/White | Ethernet RX+ | LAN8720A RXP |
| 4 | Blue | **+5V Power** | Buck converter 5V (direct, ≥5.0A total) |
| 5 | Blue/White | **GND** | Common ground |
| 6 | Green | Ethernet RX- | LAN8720A RXN |
| 7 | Brown/White | **ADC** | MCU ADC pin via adapter (parent ECU only) |
| 8 | Brown | **PWM** | MCU PWM pin via adapter (parent ECU only) |

**Cable Requirements:**
- Standard straight-through Cat5e/Cat6 (T568B both ends)
- **All 8 wires required** - Do not use 4-wire cables (some budget/flat Ethernet cables only include wires for pins 1-2, 3-6)
- Pins 4-5 are required for power (5V and GND) when connecting powered child devices
- Pins 7-8 are required for ADC/PWM functionality
- 24-26 AWG, UTP or STP
- Tested up to 50m (100m for light loads)
- **Note:** While 100 Mbps Ethernet only requires 4 wires (pins 1-3, 6), Driver Shield aux ports use all 8 wires for power and I/O functionality

**Usage:**
- **Child ECUs (Pi/Jetson):** Connect via Ethernet (pins 1-3, 6). Use device's native ADC/PWM. Communication via UDP binary protocol.
- **Parent ECU I/O:** Access ADC/PWM on pins 7-8 for direct hardware control (ESP32/STM32/Arduino native).

**Pin Remapping Note:**
- Pins 7 and 8 on all aux ports (J5-J8) have been remapped compared to Universal Shield:
  - **Pin 7 (ADC):** J5 uses GPIO8, J6 uses GPIO1, J7 uses GPIO7, J8 uses GPIO6
  - **Pin 8 (PWM):** J5 uses GPIO16, J6 uses GPIO21, J7 uses GPIO2, J8 uses GPIO15
  - This remapping improves PCB routing and frees GPIO4/5 for motor driver current sense

<details>
<summary><strong>Power Safety</strong></summary>

<div style="margin-left: 20px;">

**Overcurrent Protection:**
- ⚠️ **PENDING:** Driver Shield requires a **4A fuse** on the aux power bus (5V rail to all 4 aux ports) - See Next Steps (v2.0 Features)
- Fuse will protect against excessive current draw from misbehaving devices or short circuits
- Fuse rating should match maximum design capacity (4A total across 4 ports)

**Per-Port Power Control:** ✅ **AVAILABLE**
- **DIP Switches:** One DIP switch per aux port (4 total) allows manual enable/disable of 5V power output on each port
- **Backfeed Protection:** Schottky diodes (MBR745) on each aux port's 5V output prevent reverse current flow
- **Power Path:** Buck converter → DIP switch → Schottky diode → Connector pin 4
- **Benefits:**
  - Prevents parallel power supply issues when connecting Driver Shield-to-Universal Shield (turn off 5V on child shield)
  - Power management: Only power child devices that need it
  - Troubleshooting: Isolate power issues per port
  - Flexible installations: Mix powered and unpowered child devices
- **Switch Labeling:** Each switch labeled (e.g., "J5 5V", "J6 5V", etc.)

**Power over Ethernet (PoE) Compatibility:**
- **Standard PoE devices (IEEE 802.3af/at/bt) are NOT compatible** with aux port power
- Standard PoE requires 48V and handshake protocol (not provided by Driver Shield)
- **Standard Raspberry Pi and Jetson Nano (without PoE HATs) are safe** - pins 4&5 are not connected internally, so 5V power is safely ignored
- **PoE HATs/add-on boards are NOT supported** - PoE controllers expect 48V and may be damaged by 5V
- **Do not use PoE-enabled devices or PoE HATs on aux ports**

**Power Safety Considerations:**
- Maximum current per port: 1.0A (4A total ÷ 4 ports)
- Devices drawing excessive current will trip the 4A fuse
- Always verify device power requirements before connecting to aux ports
- For detailed power safety information, see [E-Stop & Safety Considerations](../../ESTOP_&_Safety_Considerations.md#pcb-power-trace-design-universal-shield)

</div>

</details>

</div>

</details>

<details>
<summary><strong>Bill of Materials</strong></summary>

<div style="margin-left: 20px;">

### Driver Shield (≈ $28-32 @ 1k pcs)

| Qty | Component | Part Number | Purpose | Unit Cost |
|-----|-----------|-------------|---------|-----------|
| 1 | Ethernet PHY | LAN8720A | 100 Mbps Ethernet | $1.50 |
| 4 | Ethernet connector (aux) | Adam Tech MTJ-883X1 | Aux ports J5-J8 (any can serve as router interface) | $0.53 × 4 |
| 1 | DC barrel jack | Kycon KLDVX-0202-A | 12-24V input, vertical mount (2.0mm center pin) | $0.60 |
| **Note:** Schematic uses KLDX-0202-A symbol (horizontal mount, available in KiCad libraries), but BOM lists KLDVX-0202-A (vertical mount) for actual manufacturing. Pin patterns are identical; only barrel orientation differs. Can be ordered separately and excluded from BOM during manufacture if needed. |
| 1 | Buck converter | LM2576HVS-5 | 12V/24V → 5V (60V max) | $3.00 |
| - | 3.3V LDO | N/A (ESP32-S3 provides 3.3V via pins 1-2) | Shield logic power from MCU | $0.00 |
| 1 | CAN transceiver | ADM3057E | Isolated CAN-FD | $5.50 |
| 1 | MCU header | 44-pin 2×22 stacking | ESP32-S3 interface | $1.20 |
| 2 | Motor driver IC | BTS7960B | Half-bridge motor driver (30A per IC) | $2.50 × 2 |
| 1 | Buffer IC | 74HC244 | Octal buffer/line driver (TSSOP-20) | $0.50 |
| 2 | Schottky diode | MBR3045PT | Flyback protection (30A dual common-cathode) | $1.20 × 2 |
| 1 | Actuator connector | Molex 1724480006 | 6-pin connector for PA-HD1-HALL actuator | $0.80 |
| - | Misc (caps, resistors, LEDs, protection) | - | Standard components + motor driver components | ~$4.00 |
| 1 (opt) | 40 mm fan | Sunon HA40101V4-1000U-A99 | Optional MCU cooling fan (12 V PWM) | $3.50 |

### Personality Adapters (Parent ECU Only)

| Platform | Adapter | Extra Components | Cost Adder | Total Cost |
|----------|---------|------------------|------------|------------|
| ESP32-S3 | Direct | None (native ADC/PWM) | $0 | ~$1 |
| STM32 | Direct | None (native ADC/PWM) | $0 | ~$1-2 |
| Arduino | 5V→3.3V | 6× TXS0108E (level shifters) | ~$7 | ~$8-9 |

**Note:** Raspberry Pi and Jetson Nano are **child ECUs** (connect via Ethernet aux ports), not adapters.

</div>

</details>

<details>
<summary><strong>Platform Support</strong></summary>

<div style="margin-left: 20px;">

**Parent ECU (via adapters):**
- ESP32-S3 (socket/through-hole) - Native ADC/PWM
- ESP32-WROOM-32 - Native ADC/PWM
- STM32 (Black Pill, Nucleo, etc.) - Native ADC/PWM
- Arduino Uno/Mega - Requires level shifters (TXS0108E)

**Child ECUs (via Ethernet aux ports):**
- Raspberry Pi 4/5 - Native GPIO/ADC/PWM, UDP communication
- Jetson Nano/Xavier NX - Native GPIO/ADC/PWM, UDP communication
- Any Ethernet-capable device - Device-dependent I/O, UDP communication

</div>

</details>

<details>
<summary><strong>Design Specifications</strong></summary>

<div style="margin-left: 20px;">

- **Aux Ports:** 4× CAT5 RJ45 (Ethernet + 5V power + 1× ADC + 1× PWM per port)
- **Motor Driver:** BTS7960 H-bridge (30A per half-bridge, 60A total)
- **Motor Power:** 24V direct passthrough from barrel jack (bypasses buck converter)
- **Hall Sensor Support:** 2× ADC channels for position feedback
- **Ethernet:** 100 Mbps full-duplex (LAN8720A)
- **Power Input:** 12V/24V (up to 29.2V for fully charged 24V LiFePO4)
- **Aux Port Power:** 5V directly from buck converter (≥5.0A total across 4 ports)
- **Shield Logic Power:** 3.3V from ESP32-S3 3.3V_OUT (≥2A capacity)
- **CAN Bus:** Isolated CAN-FD (ADM3057E, 3kV isolation)
- **Connectors:** All vertical mount with tall shells (16.38mm) for potting
- **Schematic Organization:** Hierarchical design with motor driver on separate sheet

</div>

</details>

<details>
<summary><strong>External Systems</strong></summary>

<div style="margin-left: 20px;">

### E-Stop Systems

**Note:** E-Stop (Emergency Stop) systems are implemented externally, upstream from the shield board. The E-Stop contactor/relay must be located as close to the battery/power supply as possible, immediately after the main circuit breaker, before the barrel jack. This ensures all power (high-current loads + shield board) is cut at the source when E-Stop is activated.

For complete E-Stop system design, sizing, compliance, and testing guidance, see: **[E-Stop & Safety Considerations](../ESTOP_&_Safety_Considerations.md)**

</div>

</details>

<details>
<summary><strong>KiCAD Workflow Notes</strong></summary>

<div style="margin-left: 20px;">

### Hierarchical Schematic Design

**Motor Driver Sheet:**
- The Driver Shield uses a hierarchical schematic design with motor driver components on a separate sheet (`motor-driver.kicad_sch`)
- The motor driver sheet is connected to the main sheet via hierarchical pins/labels
- All motor driver components (BTS7960, 74HC244, MBR3045PT, resistors, capacitors, Molex connector) are located on Sheet 2
- Power rails (24V, 5V, 3.3V, GND) are passed through hierarchical labels

### Component Re-indexing

**Note:** All components have been re-indexed compared to Universal Shield. Component references may differ from Universal Shield documentation. Always refer to the schematic for current reference assignments.

**Current Component Reference Assignments (Sheet 1):**
- **U1** - LM2576HVS-5 (Buck converter)
- **U2-U5** - MTJ-883X1 (Aux ports J5-J8, references U2, U3, U4, U5 in schematic)
- **U6** - ESP32-S3-2x22 (MCU interface, 44-pin header)
- **U7** - ADM3057ExRW (CAN transceiver)
- **U8** - LAN8720A (Ethernet PHY)

**Motor Driver Component References (Sheet 2):**
- **U9-U10** - BTS7960B (Motor driver ICs)
- **U11** - 74HC244 (Buffer IC)
- **D10** - MBR3045PT (Schottky diode - dual common-cathode package)
- **J5** - Molex 1724480006 (Actuator connector, 6-pin)
- **R13-R22** - Motor driver resistors (pull-downs, voltage dividers, pull-ups)
- **C19-C22** - Motor driver capacitors (decoupling and bulk capacitance)
- Note: All component references have been re-indexed compared to Universal Shield

### ESP32 Module Placement for Net Assignment

**Important:** If a component in the schematic is planned to be replaced with headers/vias on the PCB (like the ESP32-S3 module), it **must still be placed on the PCB first** before deletion to ensure correct net assignments.

**Problem:**
- Components marked as `(power)` symbols or with `#` prefix in their Reference (e.g., `"#U02"`) are treated as "virtual" components
- Virtual components are **not placed on the PCB** when using "Update PCB from Schematic"
- This causes all nets connected to that component's pins to be incorrectly assigned or missing

**Solution Workflow:**
1. **Remove virtual component markers** from the schematic:
   - Remove `(power)` attribute from the symbol definition in the schematic
   - Remove `#` prefix from the Reference property (e.g., change `"#U02"` to `"U02"`)
2. **Update PCB from Schematic** (Tools → Update PCB from Schematic, or F8)
   - The component will now appear in the PCB with correct net assignments
3. **Delete the component from the PCB** after nets are assigned
   - Replace with headers, vias, or other footprints as needed
   - The net connections will remain correct

**Why This Matters:**
- KiCAD uses the component's footprint and pin assignments to create the netlist
- Without the component on the PCB, nets connected to its pins cannot be properly assigned
- This causes cascading net assignment errors throughout the board

</div>

</details>

<details>
<summary><strong>Research Folder</strong></summary>

<div style="margin-left: 20px;">

PCB R&D, analysis documents, and troubleshooting guides are in the `Research/` subfolder:
- Power architecture analysis and options
- Component finding/creation guides
- KiCAD setup and troubleshooting
- CAN bus wiring and connector research
- Connector selection guides
- Motor driver component research (BTS7960, MBR3045PT, Molex connectors)

</div>

</details>

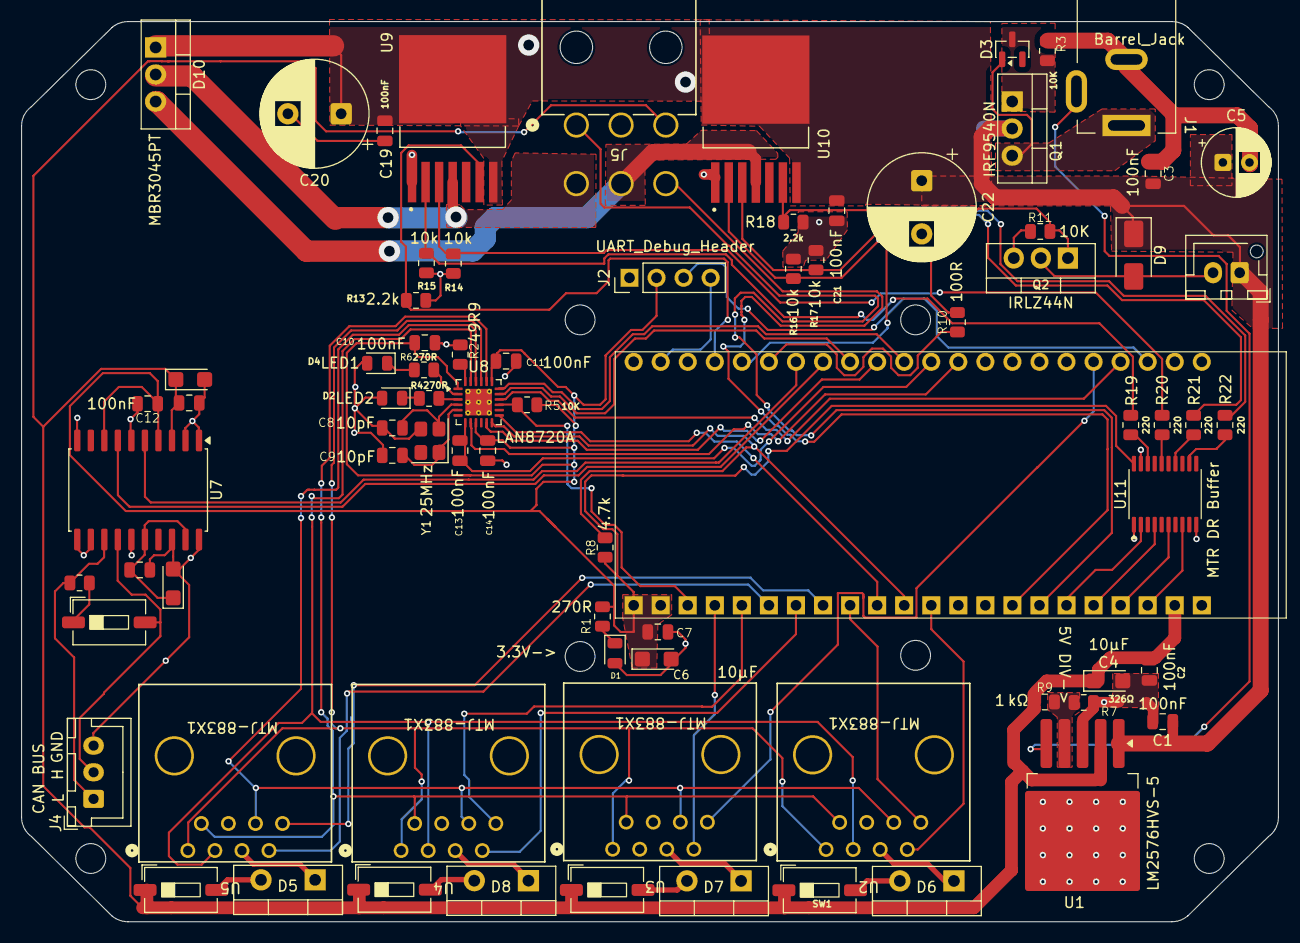
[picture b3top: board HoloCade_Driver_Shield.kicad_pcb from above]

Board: 2 copper layers, 118.0 x 84.5 mm, 78 parts (0 on the bottom side), 67 nets.

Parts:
C1, C2, C3, C7, C10, C11, C12, C13, C14, C15, C17, C19, C21: 100nF; C_0805_2012Metric
C4, C6: 10µF; CP_EIA-3216-18_Kemet-A
C5: 10µF; CP_Radial_D6.3mm_P2.50mm
C8, C9: 10pF; C_0805_2012Metric
C16, C18: 4.7µF; CP_EIA-3216-18_Kemet-A
C20, C22: 47µF; CP_Radial_D10.0mm_P5.00mm
D1: LED; LED_0805_2012Metric
D2: LED2; LED_0805_2012Metric
D3: BZX84C12; SOT-23
D4: LED1; LED_0805_2012Metric
D5, D6, D7, D8: MBR735; TO-220-2_Vertical
D9: SS14; D_SMA
D10: MBR3045PT; TO-220-3_Vertical
J1: Barrel_Jack; BarrelJack_Kycon_KLDX-0202-xC_Horizontal
J2: UART_Debug_Header; PinHeader_1x04_P2.54mm_Vertical
J3: JST-XH Fan; JST_XH_B2B-XH-AM_1x02_P2.50mm_Vertical
J4: CAN BUS; JST_XH_B3B-XH-A_1x03_P2.50mm_Vertical
J5: 1724480006; CONN_SD-172448-0000_06_MOL
Q1: IRF9540N; TO-220-3_Vertical
Q2: IRLZ44N; TO-220-3_Vertical
R1, R4, R6: 270R; R_0805_2012Metric
R2: 49R9; R_0805_2012Metric
R3, R11: 10K; R_0805_2012Metric
R5, R13, R14, R16, R17: 10k; R_0805_2012Metric
R7: 326Ω; R_0805_2012Metric
R8: 4.7k; R_0805_2012Metric
R9: 1 kΩ; R_0805_2012Metric
R10: 100R; R_0805_2012Metric
R12: 120R; R_0805_2012Metric
R15, R18: 2.2k; R_0805_2012Metric
R19, R20, R21, R22: 220; R_0805_2012Metric
SW1: J5_PWR_SW; SW_DIP_SPSTx01_Slide_6.7x4.1mm_W6.73mm_P2.54mm_LowProfile_J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
SW2: J6_PWR_SW; SW_DIP_SPSTx01_Slide_6.7x4.1mm_W6.73mm_P2.54mm_LowProfile_J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
SW3: J7_PWR_SW; SW_DIP_SPSTx01_Slide_6.7x4.1mm_W6.73mm_P2.54mm_LowProfile_J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
SW4: J8_PWR_SW; SW_DIP_SPSTx01_Slide_6.7x4.1mm_W6.73mm_P2.54mm_LowProfile_J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
SW5: SW_DIP_x01; SW_DIP_SPSTx01_Slide_6.7x4.1mm_W6.73mm_P2.54mm_LowProfile_J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
U1: LM2576HVS-5; TO-263-5_TabPin3
U2, U3, U4, U5: MTJ-883X1; CONN_MTJ-883X1_ADM
U6: ESP32-S3-2x22; ESP32-S3_2x22_Header_v3
U7: ADM3057ExRW; SOIC-20W_7.5x12.8mm_P1.27mm
U8: LAN8720A; VQFN-24-1EP_4x4mm_P0.5mm_EP2.5x2.5mm_ThermalVias
U9, U10: BTS7960B; DPAK127P1490X440-8N
U11: MTR DR Buffer; TSSOP-20_4.4x6.5mm_P0.65mm
Y1: 25MHz; Crystal_SMD_3225-4Pin_3.2x2.5mm

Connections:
+3.3V: C6.1, C7.1, C11.1, C14.1, J2.2, R1.2, R5.1, R8.1, U6.1 (VDD3P3), U6.2 (VDD3P3_2), U7.4 (VIO), U7.8 (STBY), U8.1 (VDD2A), U8.6 (VDDCR), U8.9 (VDDIO), U8.19 (VDD1A), U11.20
+5V: C2.2, C4.1, C15.1, C16.1, J5.3, U1.2 (OUT), U6.21 (VIN), U7.3 (VCC)
+24_12V: C1.1, C3.2, C5.1, C19.1, C20.1, C21.1, C22.1, D9.1 (K), D10.1 (C), J3.1, Q1.2 (D), U1.1 (VIN), U9.7 (VS), U9.8 (VS), U10.7 (VS), U10.8 (VS)
/FAN_SW: D9.2 (A), J3.2, Q2.2 (D)
/IO1: R15.1, U6.26 (GPIO1), U9.6 (IS)
/IO2: R18.1, U6.27 (GPIO2), U10.6 (IS)
/IO4: U3.7, U6.4 (GPIO4)
/IO5: U4.8, U6.5 (GPIO5)
/IO6: U5.7, U6.6 (GPIO6)
/IO7: U4.7, U6.7 (GPIO7)
/IO8: U2.7, U6.12 (GPIO8)
/IO9: J5.6, U6.15 (GPIO9)
/IO10: J5.1, U6.16 (GPIO10)
/IO11: U6.17 (GPIO11), U11.2
/IO12: U6.18 (GPIO12), U11.4
/IO13: U6.19 (GPIO13), U11.6
/IO14: U6.20 (GPIO14), U11.8
/IO15: U5.8, U6.8 (GPIO15)
/IO16: U2.8, U6.9 (GPIO16)
/IO17: U6.10 (GPIO17), U8.13 (MDC)
/IO18: R8.2, U6.11 (GPIO18), U8.12 (MDIO)
/IO20: U6.41 (GPIO20), U8.16 (TXEN)
/IO21: U3.8, U6.40 (GPIO21)
/IO24: J2.4, U6.24 (U0TXD)
/IO35: U6.35 (GPIO35), U8.8 (RXD0/MODE0)
/IO36: U6.34 (GPIO36), U8.7 (RXD1/MODE1)
/IO37: U6.33 (GPIO37), U8.18 (TXD1)
/IO38: U6.32 (GPIO38), U8.11 (CRS_DV/MODE2)
/IO39: U6.31 (GPIO39), U8.17 (TXD0)
/IO40: U6.30 (GPIO40), U7.7 (TXD)
/IO41: U6.29 (GPIO41), U7.5 (RXD)
/IO42: R10.1, U6.28 (GPIO42)
/IO44: J2.3, U6.42 (U0RXD)
/JACK_SW: J1.3, U1.5 (~ON/OFF)
/LED1: R4.1, U8.3 (LED1/REGOFF)
/LED2: R6.1, U8.2 (LED2/~INTSEL)
/Motor Driver Sheet/BTS_A_EN: R14.1, R20.2, U9.3 (INH)
/Motor Driver Sheet/BTS_A_IN: R13.1, R19.2, U9.2 (IN)
/Motor Driver Sheet/BTS_B_EN: R17.1, R22.2, U10.3 (INH)
/Motor Driver Sheet/BTS_B_IN: R16.1, R21.2, U10.2 (IN)
/Motor Driver Sheet/MOTOR_A_OUT: D10.2 (A1), J5.4, U9.4 (OUT)
/Motor Driver Sheet/MOTOR_B_OUT: D10.3 (A2), J5.5, U10.4 (OUT)
/RESET_N: R5.2, U6.3 (EN), U8.15 (~RST)
/RX+: U2.3, U3.3, U4.3, U5.3, U8.23 (RXP)
/RX-: U2.6, U3.6, U4.6, U5.6, U8.22 (RXN)
/TX+: U2.1, U3.1, U4.1, U5.1, U8.21 (TXP)
/TX-: U2.2, U3.2, U4.2, U5.2, U8.20 (TXN)
GND: C1.2, C2.1, C3.1, C4.2, C5.2, C6.2, C7.2, C11.2, C14.2, C15.2, C16.2, C19.2, C20.2, C21.2, C22.2, D1.2 (A), J1.2, J2.1, J5.2, Q2.3 (S), R11.1, R13.2, R14.2, R15.2, R16.2, R17.2, R18.2, U1.3 (GND), U2.4, U3.4, U4.4, U5.4, U6.22 (GND), U6.23 (GND), U6.43 (GND), U6.44 (GND), U7.1 (GND1), U7.2 (GND1), U7.6 (SILENT), U7.10 (GND1), U7.11 (GND2), U7.12 (RS), U7.15 (GND2), U8.25 (VSS), U9.1 (GND), U10.1 (GND), U11.1, U11.10, U11.19
unnamed: D1.1 (K), R1.1
unnamed: D3.1 (A), J1.1, Q1.3 (S)
unnamed: D3.3 (K), Q1.1 (G), R3.2
unnamed: D5.1 (K), U5.5
unnamed: D6.1 (K), U2.5
unnamed: D7.1 (K), U3.5
unnamed: D8.1 (K), U4.5
unnamed: J4.1, R12.1, U7.13 (CANL)
unnamed: J4.2, U7.14 (CANH)
unnamed: C17.2, C18.2, J4.3, U7.18 (GNDISO), U7.20 (GNDISO)
unnamed: Q2.1 (G), R10.2, R11.2
unnamed: R7.2, R9.1, U1.4 (FB)
unnamed: C17.1, C18.1, U7.16 (VISOIN), U7.19 (VISOOUT)
unnamed: U8.5 (XTAL1/CLKIN), Y1.1
unnamed: U8.4 (XTAL2), Y1.2
unnamed: R19.1, U11.18
unnamed: R20.1, U11.16
unnamed: R21.1, U11.14
unnamed: R22.1, U11.12

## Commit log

2026-04-07 initial commit after name change from LBEAST to HoloCade
    Made-with: Cursor
2026-04-14 Add arcade cabinet IO (Unity parity), UDP transport simple, hide UDP delegates in Details
    - UArcadeCabinetBridge, UArcadeCabinetIOConfig, FPlayerSlotIoBindings, FCabinetConfigPresets
    - UHoloCadeUDPTransportSimple: concrete transport for plain HoloCade UDP
    - HoloCadeUDPTransport: HideInDetailPanel on receive multicast delegates
    - Plugin version 1.0.1 (Version 2)
    Made-with: Cursor
2026-04-14 Add Cabinet NEXT_STEPS.md (SDK diagnostics and boot entry roadmap)
    Made-with: Cursor
